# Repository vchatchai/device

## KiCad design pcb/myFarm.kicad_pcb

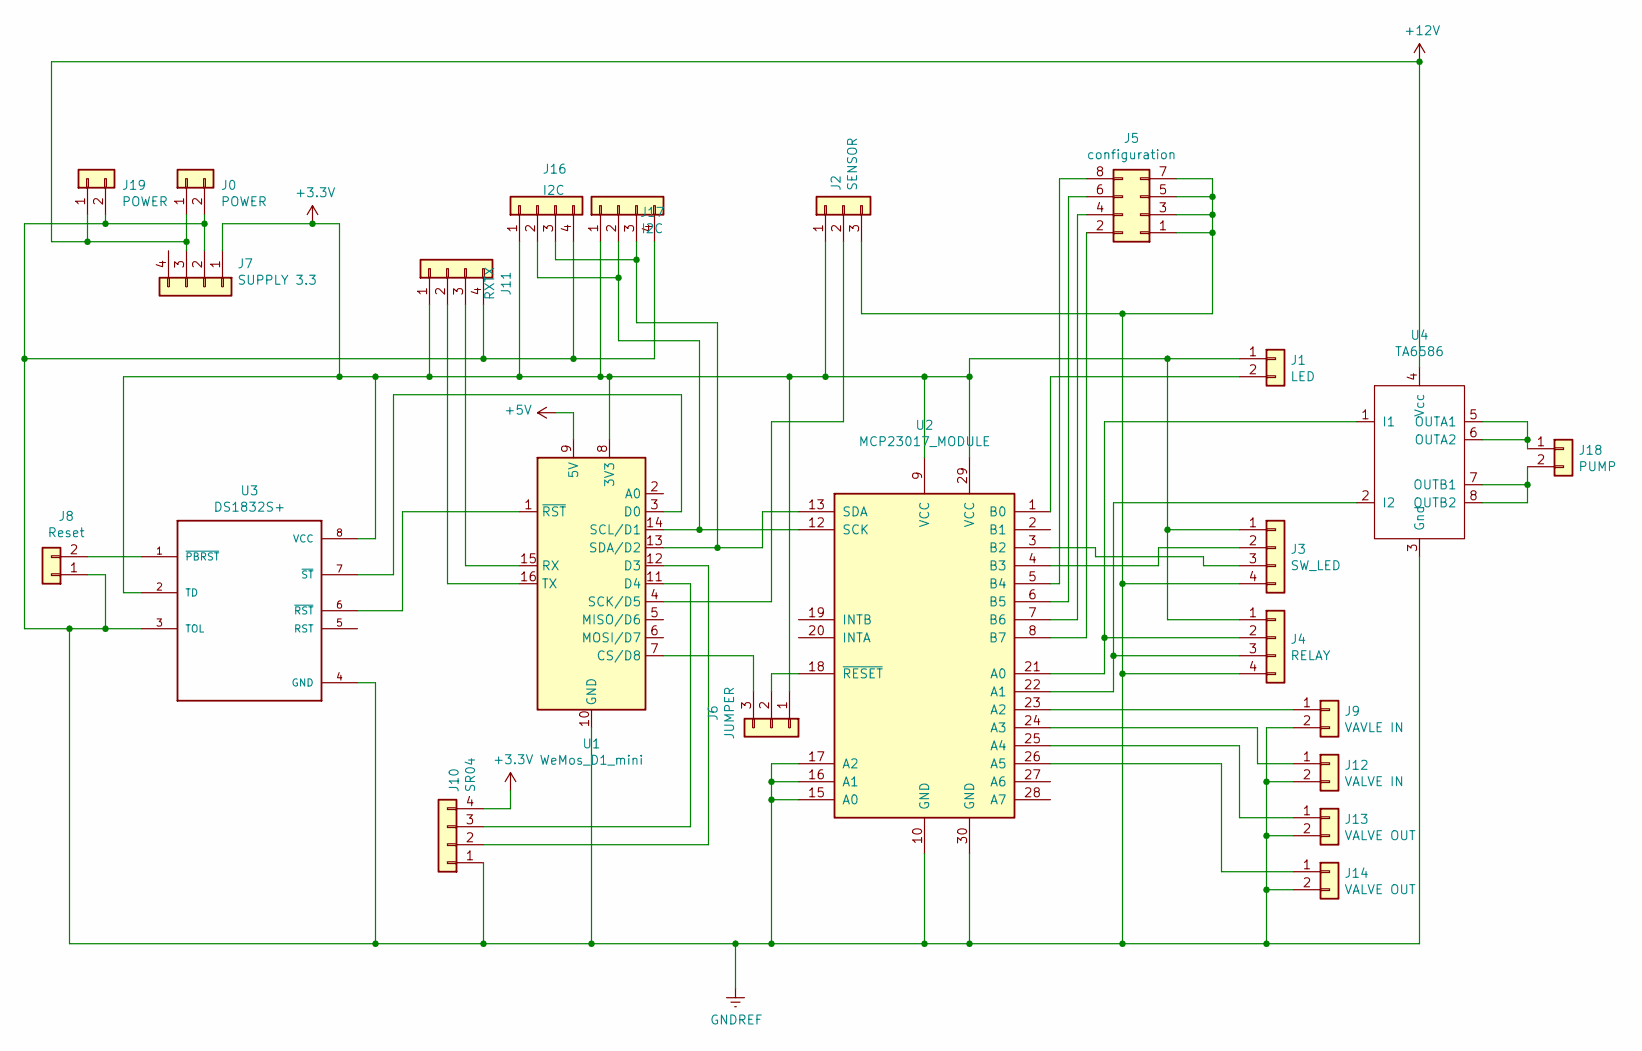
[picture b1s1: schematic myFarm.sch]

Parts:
J0: POWER; JST_XH_B2B-XH-A_1x02_P2.50mm_Vertical
J1: LED; JST_XH_B2B-XH-A_1x02_P2.50mm_Vertical
J2: SENSOR; JST_XH_B3B-XH-A_1x03_P2.50mm_Vertical
J3: SW_LED; JST_XH_B4B-XH-A_1x04_P2.50mm_Vertical
J4: RELAY; JST_XH_B4B-XH-A_1x04_P2.50mm_Vertical
J5: configuration; PinHeader_2x04_P2.00mm_Vertical
J6: JUMPER; PinHeader_1x03_P2.54mm_Vertical
J7: SUPPLY 3.3; JST_XH_B4B-XH-A_1x04_P2.50mm_Vertical
J8: Reset; JST_XH_B2B-XH-A_1x02_P2.50mm_Vertical
J9: VAVLE IN; JST_XH_B2B-XH-A_1x02_P2.50mm_Vertical
J10: SR04; JST_XH_B4B-XH-A_1x04_P2.50mm_Vertical
J11: RXTX; JST_XH_B4B-XH-A_1x04_P2.50mm_Vertical
J12: VALVE IN; JST_XH_B2B-XH-A_1x02_P2.50mm_Vertical
J13, J14: VALVE OUT; JST_XH_B2B-XH-A_1x02_P2.50mm_Vertical
J16, J17: I2C; JST_XH_B4B-XH-A_1x04_P2.50mm_Vertical
J18: PUMP; SolderWirePad_1x02_P7.62mm_Drill2.5mm
J19: POWER; SolderWirePad_1x02_P7.62mm_Drill2.5mm
U1: WeMos_D1_mini; WEMOS_D1_mini_light
U2: MCP23017_MODULE; MCP23017-MODULE
U3: DS1832S+; DIP-8_W7.62mm_Socket
U4: TA6586; DIP-8_W7.62mm_Socket

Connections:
+3V3: J1.1, J2.1, J3.1, J4.1, J6.1, J7.1, J10.4, J11.1, J16.1, J17.1, U1.8 (3V3), U2.9 (VCC), U2.29 (VCC), U3.2 (TD), U3.8 (VCC)
+12V: J0.1, J7.3, J19.1, U4.4 (Vcc)
GNDREF: J0.2, J2.3, J3.4, J4.4, J5.1, J5.3, J5.5, J5.7, J7.2, J8.1, J9.2, J10.1, J11.4, J12.2, J13.2, J14.2, J16.4, J17.4, J19.2, U1.10 (GND), U2.10 (GND), U2.15 (A0), U2.16 (A1), U2.17 (A2), U2.30 (GND), U3.3 (TOL), U3.4 (GND), U4.3 (Gnd)
unnamed: J1.2, U2.1 (B0)
unnamed: J2.2, U1.4 (SCK/D5)
unnamed: J3.2, U2.4 (B3)
unnamed: J3.3, U2.3 (B2)
unnamed: J4.2, U2.21 (A0), U4.1 (I1)
unnamed: J4.3, U2.22 (A1), U4.2 (I2)
unnamed: J5.2, U2.8 (B7)
unnamed: J5.4, U2.7 (B6)
unnamed: J5.6, U2.6 (B5)
unnamed: J5.8, U2.5 (B4)
unnamed: J6.2, U2.18 (~RESET~)
unnamed: J6.3, U1.7 (CS/D8)
unnamed: J8.2, U3.1 (~PBRST~)
unnamed: J9.1, U2.23 (A2)
unnamed: J10.2, U1.12 (D3)
unnamed: J10.3, U1.11 (D4)
unnamed: J11.2, U1.16 (TX)
unnamed: J11.3, U1.15 (RX)
unnamed: J12.1, U2.24 (A3)
unnamed: J13.1, U2.25 (A4)
unnamed: J14.1, U2.26 (A5)
unnamed: J16.2, J17.2, U1.14 (SCL/D1), U2.12 (SCK)
unnamed: J16.3, J17.3, U1.13 (SDA/D2), U2.13 (SDA)
unnamed: J18.1, U4.5 (OUTA1), U4.6 (OUTA2)
unnamed: J18.2, U4.7 (OUTB1), U4.8 (OUTB2)
unnamed: U1.1 (~RST), U3.6 (~RST~)
unnamed: U1.3 (D0), U3.7 (~ST~)

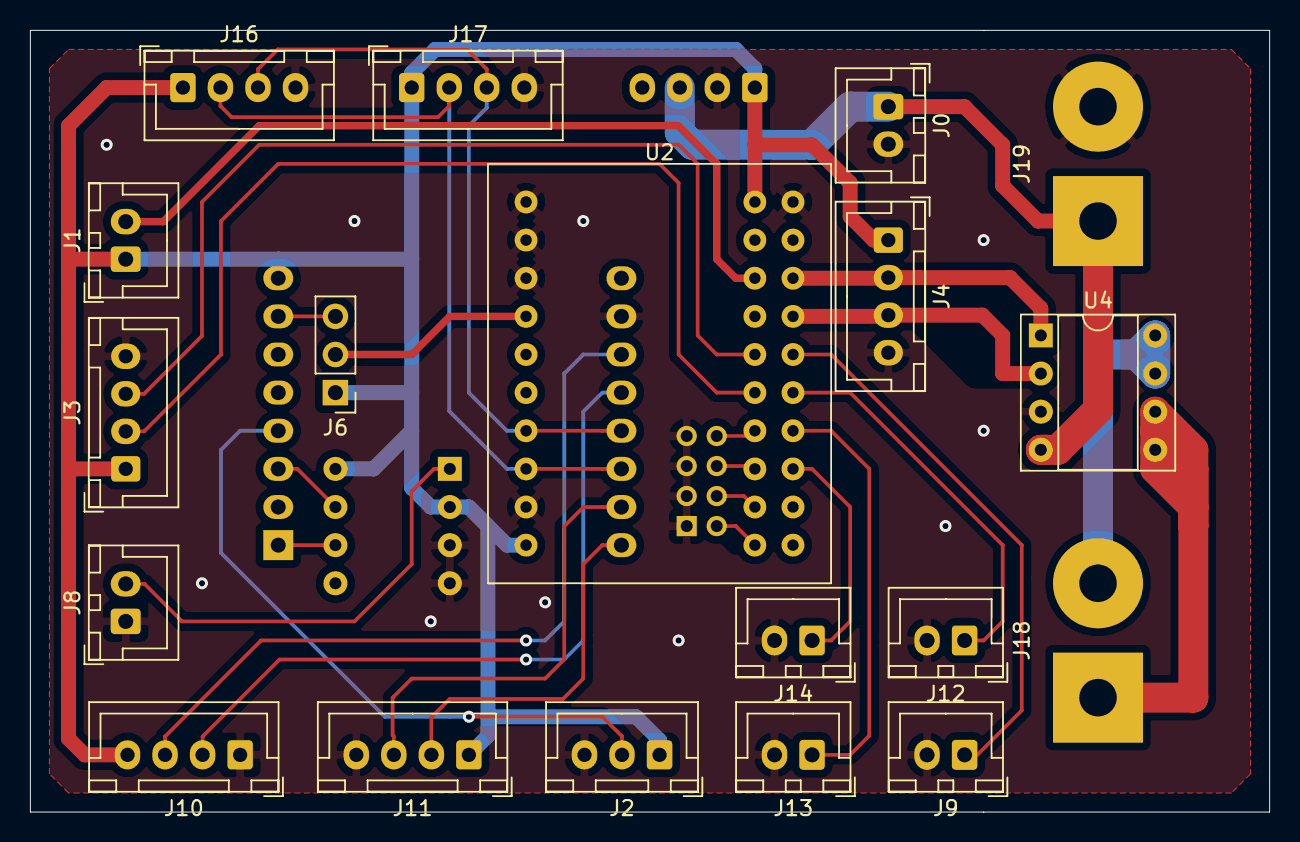
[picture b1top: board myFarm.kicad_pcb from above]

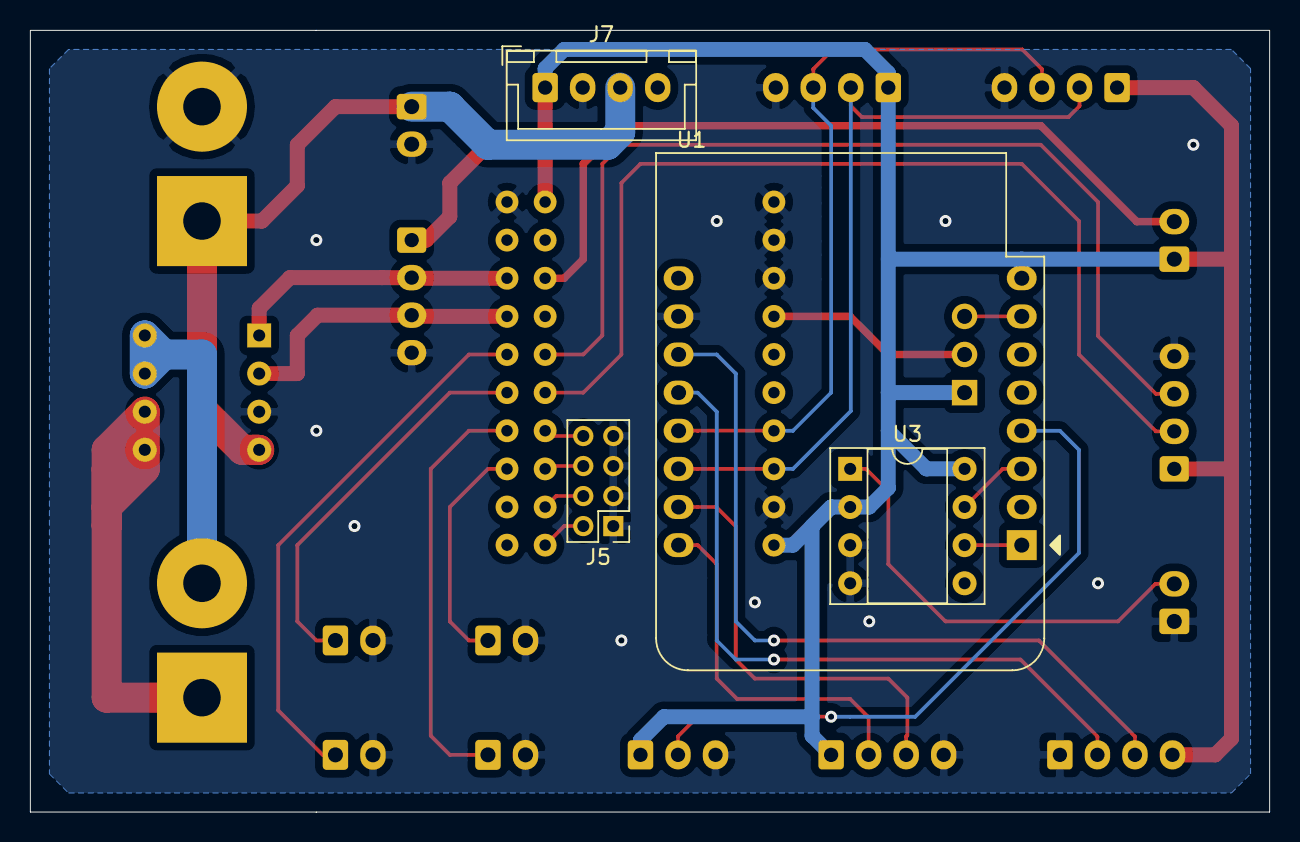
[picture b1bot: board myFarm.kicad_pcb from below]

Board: 2 copper layers, 82.6 x 52.1 mm, 23 parts (4 on the bottom side), 30 nets.

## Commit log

2019-06-17 Initial V2
2019-06-17 update files
2019-07-11 support MCP23017.
2019-07-16 add schematic and pcb.
2019-07-29 update port
2019-07-30 update pcb
2019-07-31 swap connect j3
2019-08-15 support dht22 sensor.
2019-08-26 update valve
2019-09-03 add watchdog
2019-09-03 update code for relay and power drive
2019-09-03 update pcb.
2019-11-18 support relay trigger.
2020-01-13 update support json size on mqtt
2020-01-13 update pcb board.
2020-03-22 add vc config.
2020-04-11 update on/off
2020-04-11 new version pcb
2020-04-12 add selector for switch
2020-05-03 update code
